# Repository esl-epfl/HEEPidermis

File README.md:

# Welcome!

HEEPidermis is a chip based on the open-source RISC-V platform [X-HEEP](https://github.com/esl-epfl/x-heep) intended to record Galvanic Skin Response (GSR) and Impedance (Z).
HEEPidermis is capable of injecting arbitrary-wave currents on the skin with an 8-bit iDAC and measure voltage through a 14-bit VCO-based ADC.
Parameters of the iDAC and ADC can be programmed dynamically using the on-board Ibex CPU. Acquired data can be stored in the 16 kB RAM memory for on-chip processing, compression, and transmission.

HEEPidermis can be interfaced through JTAG for code-debugging, SPI to obtain recordings from memory, or UART.
External ADCs and peripherals can also be commanded via SPI.

The Direct Memory Access (DMA) block allows the chip to operate autonomously without the constant interaction of the CPU. Given proper configuration, the DMA can take care of controlling the current injection profile, read data from the local ADC (or an external one), store data and/or transmit it through SPI.
The DMA can additionally re-direct data to a digital Level Crossing (dLC) block to filter data and reduce the output data rate. The output of the dLC can be stored in memory (along timestamps) or be exposed to be used as feedback loop for the analog front-end, interface with transmission circuits or as input to Spiking Neural Networks.
The dLC block also accepts inputs from analog LC ADCs (instead of the on-chip ADC).

HEEPidermis can also decimate 1-bit ΔΣ-ADCs' output with an integrated CIC filter or, alternatively, with an integrated custom smoothing stage, followed by the dLC block.

Being based on the X-HEEP platform, you can check its documentation on how to program, debug, or understand how it was built. We suggest using the [vendorized X-HEEP's documentation](../../hw/vendor/x-heep/docs/source/index.rst).
For all HEEPidermis-specific documentation, please refer to the documentation below.

<p align="center">

&nbsp;&nbsp;&nbsp;

</p>

## Index

- **Analog Front End**
  - [Analog subsystem](hw/ip/analog_subsystem/README.md)
  - [iDAC](hw/vendor/analog-library/iDAC/docs/README.md)
  - [VCO](hw/vendor/analog-library/VCO/docs/README.md)

- **Digital Back End**
  - [CPU](./docs/source/DBE/CPU.md)
  - [DMA (how we use it)](./docs/source/DBE/DMA.md)
  - [DMA](hw/vendor/x-heep/docs/source/Peripherals/DMA.md)
  - [SPI host](hw/vendor/x-heep/docs/source/Peripherals/SPI.md)
  - [SPI slave](hw/vendor/x-heep/docs/source/Peripherals/SPI_slave.md)
  - [digital Level-Crossing](hw/vendor/x-heep/docs/source/ExternalPeripherals/dLC.md)
  - [ΔΣ decimation (CIC filter)](./docs/source/DBE/CIC_filter.md)
  - [ΔΣ decimation (SES filter)](./docs/source/DBE/SES_filter.md)

- **PCBs**
  - [CHEEP-boards](./hw/vendor/cheep-boards/) - To program and provide power
  - [Breakout board](./hw/vendor/breakout-board/) - To solder the cheep and connect it to the CHEEP-boards.

- **Software**
  - [Desktop GUI](./sw/gui/README.md) - multi-device acquisition workspace (HEEPidermis board control, VCO GSR recordings, BIOPAC)

- **Reference**
  - [Register index](./docs/source/Register_index.md) - full register map of the external peripherals (iDAC, VCO decoder, REFs, aMUX, dLC, CIC, SES) with names, C-definable aliases, addresses, bit fields, reset values and descriptions. Intended to configure the cheep from an external master (e.g. an Arduino) through the SPI slave.

- **Related documents**
  - [HEEPidermis](https://arxiv.org/abs/2509.04528)
  - [ΔΣ Decimation theory](https://ieeexplore.ieee.org/abstract/document/11044062)
  - [iDAC precursor](https://ieeexplore.ieee.org/document/11044212)
  - [VCO Design](https://arxiv.org/abs/2509.06698)

## Desktop GUI

HEEPidermis includes a desktop GUI to configure the board, build firmware, record GSR signals, and visualize and analyze recordings. Adjust the injected current and sampling frequency live, explore saved recordings, and export your data to CSV.

Launch it from the repository root with:

```sh
make gui
```

See the [GUI documentation](./sw/gui/README.md) for installation requirements and usage instructions.

## BIOPAC live GUI

An experimental native Linux acquisition layer records and plots EDA from a
BIOPAC MP160 (with EDA100C or BioNomadix PPGED-R) over UDP, with live
voltage/conductance/tonic-phasic plots, manual amplifier gain and filter
declarations, and verified, autosaved sessions. No Windows, Wine, or BHAPI DLL
is required. It runs inside the desktop workspace (`make gui`, enable BIOPAC in
the device list) or standalone:

```sh
make biopac            # current BioNomadix setup: channel 9, 100 Hz, 5 µS/V
BIOPAC_ARGS=--demo make biopac   # explicitly labelled simulation
```

See the [BIOPAC documentation](./sw/gui/sdk/biopac/README.md) for setup, calibration, and safety notes.

## Evaluating trade-offs in GSR recording

HEEPidermis is a complex SoC, and acquiring GSR keepeing a proper range, sensitivity, dynamic range, resolution and power can be very tricky! To aid in the process of choosing the right parameters we have modeled the performance and consumption of our front-end and integrated it into a visual model with which you can play.

You can use the plotter in two different ways:

1. **Forward control**: You choose the operating variables (injected current and sampling frequency) and study the obtained sensitivity for a given baseline value of conductivity (G)
2. **Target**: You select a target sensitivty and power consumption and let the tool find the optimal configuration.

To view the interactive plotter on your browser (forward mode only) run:
```
make plotter
```

## Making a GSR recording

We make GSR recordings by biasing the skin to the LDO's output at 0.8 V and using a second electrode to train current from the skin using the iDAC. The VCO measures that same node and the CPU computes the drop (knowing the LDO's output).

Because the computation is far from trivial we have added [a GSR SDK](./sw/external/lib/sdk/GSR) that takes care of managing peripherals and parameters to do the correct conversion to skin's conductance in nS. You can run the example application:

```
make app PROJECT=test_reconstruction BOOT_MODE=force
make verilator-run BOOT_MODE=force # Takes long, be patient :P (or cancel anytime with Ctrl+C and go ahead with the next step)
make verilator-waves
```

You will be able to see the input resistance (in Ω) and at the top (in yellow) the computed conductance (in nS). This simulation uses the behavioral models of the front-end, including an approximation of the VCO's measured phase noise.

## Prerequisites

Since this project is based on _X-HEEP_, it has the same prerequisites.

1. Follow _X-HEEP_'s [_Prerequisite_](https://github.com/esl-epfl/x-heep/tree/main#prerequisite) section to download the necessary tools.
To correctly generate hardware and software, an extended version of the _core-v-mini-mcu_ environment is required. To install it run:
   ```Bash
   make conda
   ```
Make sure the Conda environment is active:
   ```Bash
   conda activate heepidermis
   ```

2. Make sure that the following tools are available in your system's `PATH`:
   - To compile code: **RISC-V toolchain version 2022.01.17**, supporting at least `rv32imc`. Newer versions will work but compilation will have a bug when reporting memory usage.
   - To format SystemVerilog (in case you want to open a PR): **Verible version 0.0-4023-gc1271a00**
   - To simulate (open source): **Verilator 4.210**
   - To see waveforms out of Verilator: **GTKWave**
   - In case you have the licences:
     - Siemens QuestaSim version 2020.4 or above
     - Synopsys Design Compiler version 2020.09 or above

You can follow the instructions on how to install these tools on the [X-HEEP documentation - Manual setup](https://x-heep.readthedocs.io/en/latest/GettingStarted/Setup.html#manual-setup).

## Preparing the Boards

The easiest way to test HEEPidermis is to use the [CHEEP-boards](./hw/vendor/cheep-boards/), which provide all the tools (sw and hardware) to supply power and program HEEPidermis.

HEEPidermis is soldered (or placed on a socket) on the [breakout board](./hw/vendor/breakout-board/).

After soldering everything, you also need to:

### Connect chewing-gums

The chewing-gum (CG) boards are small shields that are connected to the main board, and which can be used to provide power or reference voltages to HEEPidermis, and measure that consumption.

| CG | Function | Nominal value | CG | Function | Nominal value |
| :--- | :--- | :--- | :--- | :--- | :--- |
| 6 | DCORE VDD | 0.8 V | 7 | ACORE VDD | 1.2 V |
| 5 | IO VDD | 1.8 V | 8 | iREF | Connect a source of 400 nA |
| 4 | not used | - | 9 | REF VDD | 1.2 V |
| 3 | not used | - | 10 | LDO VREF | 0.8 V |
| 2 | not used | - | 11 | VCO VDD | 0.8 V |
| 1 | not used | - | 12 | LDO VDD | 1.2 V |

> _Note that the bottom three CGs on the picture below are not used, they are just used to inject voltages here and there with an external cable for testing._

⚠️ Remember to solder a shunt resistor below the CG! ~10 Ω should do fine for the range 1-100 µW. Consider that the INA will amplify the drop by 1000-2000×, has an offset of some 10s µV, and it cannot output more than 3.3 V.

### Connect jumpers and switches

On the main board
* Each CG has three jumpers. To control them with the trimmer, connect the jumper next to it towards its screw. Connect the jumper on the side away from the trimmer to turn the power on. Connect the jumper innermost to the main baord away from the test point to make the output go to the main board.
* Connect the jumper for the IO VDD (next to CG 8) on 1.8 V
* No need to connect any jumper next to the oscilaltor (bottom of the main board)

On the breakout board there are several places where to connect jumpers to use the cheep on different configurations. Mainly, there are two rulers of pin headers around the cheep which can be used to connect or disconnect supplies. Many of them are short-circuited on both sides, so you just use the headers as test points or to inject a signal. The rest are marked with what would get to the cheep if you close the jumper. Additionally there are three-pin jumpers for you to choose what to supply the cheep with: an ideal supply coming from the main board's chewing gums, or a voltage/current coming from the on-cheep supplies.

Check the table on [the breakout board's readme](./hw/vendor/cheep-boards/) to see what connects what.

> ❗There are two pads on the bottom of the board that need to be short-circuited: They will connect the clock input to the cheep. You can select where to take the clock, if you have no clue what to do, put some solder tin on the two pair of pads that point to the main board to take the clock from there. Don't worry if you make a mistake and short a bit the other, it's not the end of the world.

There is a pair of switches on the breakout board, to the left of the cheep. You can eiter solder the switches to select the boot mode, or you can short with tin them the mid-pin with the one closest to the cheep to only use JTAG mode (explained below).

### Bug correction

🪲 You need to cut the pin below the `value` pin (the outter most pin, in row 31 of the main board) in the connector to the main board or nothing will work, sorry.

## Programming the ASIC

You can program the ASIC through 3 alternatives:
 - JTAG
 - Loading an external flash that HEEPidermis can read through SPI
 - Loading the program in RAM through the SPI slave peripheral

### Programming through JTAG

You need to connect the JTAG interface to an FTDI chip. This is avaialble on the [EPFL programmer](https://github.com/esl-epfl/x-heep-programmer-pmod) or on the [CHEEP boards](https://eslgit.epfl.ch/heep/cheep-boards) (currently only available upon request).

1. The BOOT switches should be set to

| Signal     | Value |
|------------|-------|
| FLASH_EXEC | 0     |
| BOOT_SEL   | 0     |

2. Set the system clock to 1 MHz. You can do that in two steps if you have the CHEEP board, and have exported the variable `$CHEEP_BOARDS` pointing to the folder where the repo is.
```bash
make board_config
make board_freq PLL_FREQ=1_000_000  #default
```

3. Build the SW/HW stack of the cheep
```bash
make cheep-gen
```

4. Compile the code
```bash
make app BOOT_MODE=jtag
```

1. Open openOCD and picocom to see the UART output
```bash
make jtag_open
```
1. Open GDB and run the program
```bash
make jtag_run
```
Useful commands:
> `c` (continue)
>
> `monitor reset hart`
>
> `monitor pc _start`
>
> `si` (next instruction)
>
> `disassembler`
>
> `x/8i` (see the following instructions).

1. Exit GDB with `ctrl+C` and type `quit`
2. Close the openOCD and uart terminals with
```bash
make jtag_close
```

### Programming from the FLASH

Testing... we seem to have a bug on the main board that prevents this from working 😬

### Programming through SPI

HEEPidermis supports SRAM programming through its SPI slave interface using a Raspberry Pi Pico. The Pico also provides a configurable external system clock.

The system supports operation from the ASIC's internal VCOp oscillator, allowing the external clock to be disconnected after initialization.

For hardware connections, programming commands, clock configuration, VCO-based clock operation, and troubleshooting, see the **[SPI Programmer and Clock Configuration Guide](./sw/arduino/README.md)**.

## RTL Simulation

The included [`makefile`](./makefile) proves all the necessary rules to build _HEEPidermis_:

1. Generate all the RTL files (and software headers):
   ```bash
   make cheep-gen
   ```
   Some _X-HEEP_ configuration parameters (e.g. `BUS`, `MEMORY_BANKS` etc.) are still supported, although the default configuration may differ (check [`peripherals_config`](./config/peripherals_config)). In general, these should not be passed through the makefile targets but should be configured in the hjson files in the `config` folder.

2. Build the simulation model:
   ```bash
   make verilator-build     # Verilator
   make questasim-build     # QuestaSim
   ```

3. The software build process is primarily handled by _X-HEEP_, and most of its [example applications](./hw/vendor/x-heep/sw/applications/) will work on _HEEPidermis_ as well. You can choose other `BOOT_MODE`, just be sure to match it with the one used with `make *-build` (by default they use `fore`). `force` will be the faster for simulation.

```bash
make app PROJECT=test_dlc_vco BOOT_MODE=force
```

The combinations of compatible linker and boot modes can be found here:

1. Launch the simulation with the compiled firmware:
   ```bash
   make verilator-run       # Verilator with waveforms dump
   make verilator-opt       # Verilator without waveforms dump
   make questasim-run       # QuestaSim
   make questasim-gui       # QuestaSim with GUI
   ```

   You can also set other parameters like the `FUSESOC_FLAGS`, `LOG_LEVEL`, `BOOT_MODE`, `VCD_MODE`, etc. to customize the simulation. Refer to the [`makefile`](./makefile) for more details.

2. _HEEPidermis_ `stdout` is exposed through a UART DPI interface at `/dev/pts/<N>`, where `N` is a number printed on the simulation log during execution. You can connect to it using `screen` or similar tools, e.g.:
   ```bash
   screen /dev/pts/0
   ```
   The UART output is also stored to the `uart.log` file in the common simulation directory (`build/sim-common/uart.log`).
   > Using `printf()` will significantly increase the firmware execution time and therefore the simulation. For quick debugging, it recommended to use the return value from `main` instead. When it is _not_ zero, the testbench will print it out at the end of the simulation.

3. The waveforms dumped during the simulation can be opened using:
   ```bash
   make verilator-waves # after Verilator simulation
   make questasim-waves # after QuestaSim simulation
   ```

This will open the waveforms (example from `test_dlc_vco` application):

Assuming that your firmware is already available, steps 1., 3., and 4. can be repeated with a single command using the `verilator-sim` or `questasim-sim` targets.

# Questions?

Have questions? curiosities? ideas on how to exploit HEEPidermis? Want to contribute on following versions of the SoC?
Drop an email :) juan.sapriza@epfl.ch

# 📄 Reference

Want to know more details? Found HEEPidermis useful for your research? Cite our [LASCAS paper](https://ieeexplore.ieee.org/document/11457136).

```
@INPROCEEDINGS{11457136,
  author={Sapriza, Juan and Grassano, Beatrice and Naclerio, Alessio and Quadri, Filippo and Terzano, Tommaso and Mallasén, David and Schiavone, Davide and Leplae, Robin and Moullet, Jérémie and Levisse, Alexandre and Müller, Christoph and Graziano, Mariagrazia and Miguez, Matías and Atienza, David},
  booktitle={2026 IEEE 17th Latin America Symposium on Circuits and System (LASCAS)},
  title={HEEPidermis: A Versatile SoC for BioZ Recording},
  year={2026},
  pages={1-5},
  doi={10.1109/LASCAS67804.2026.11457136}}
```

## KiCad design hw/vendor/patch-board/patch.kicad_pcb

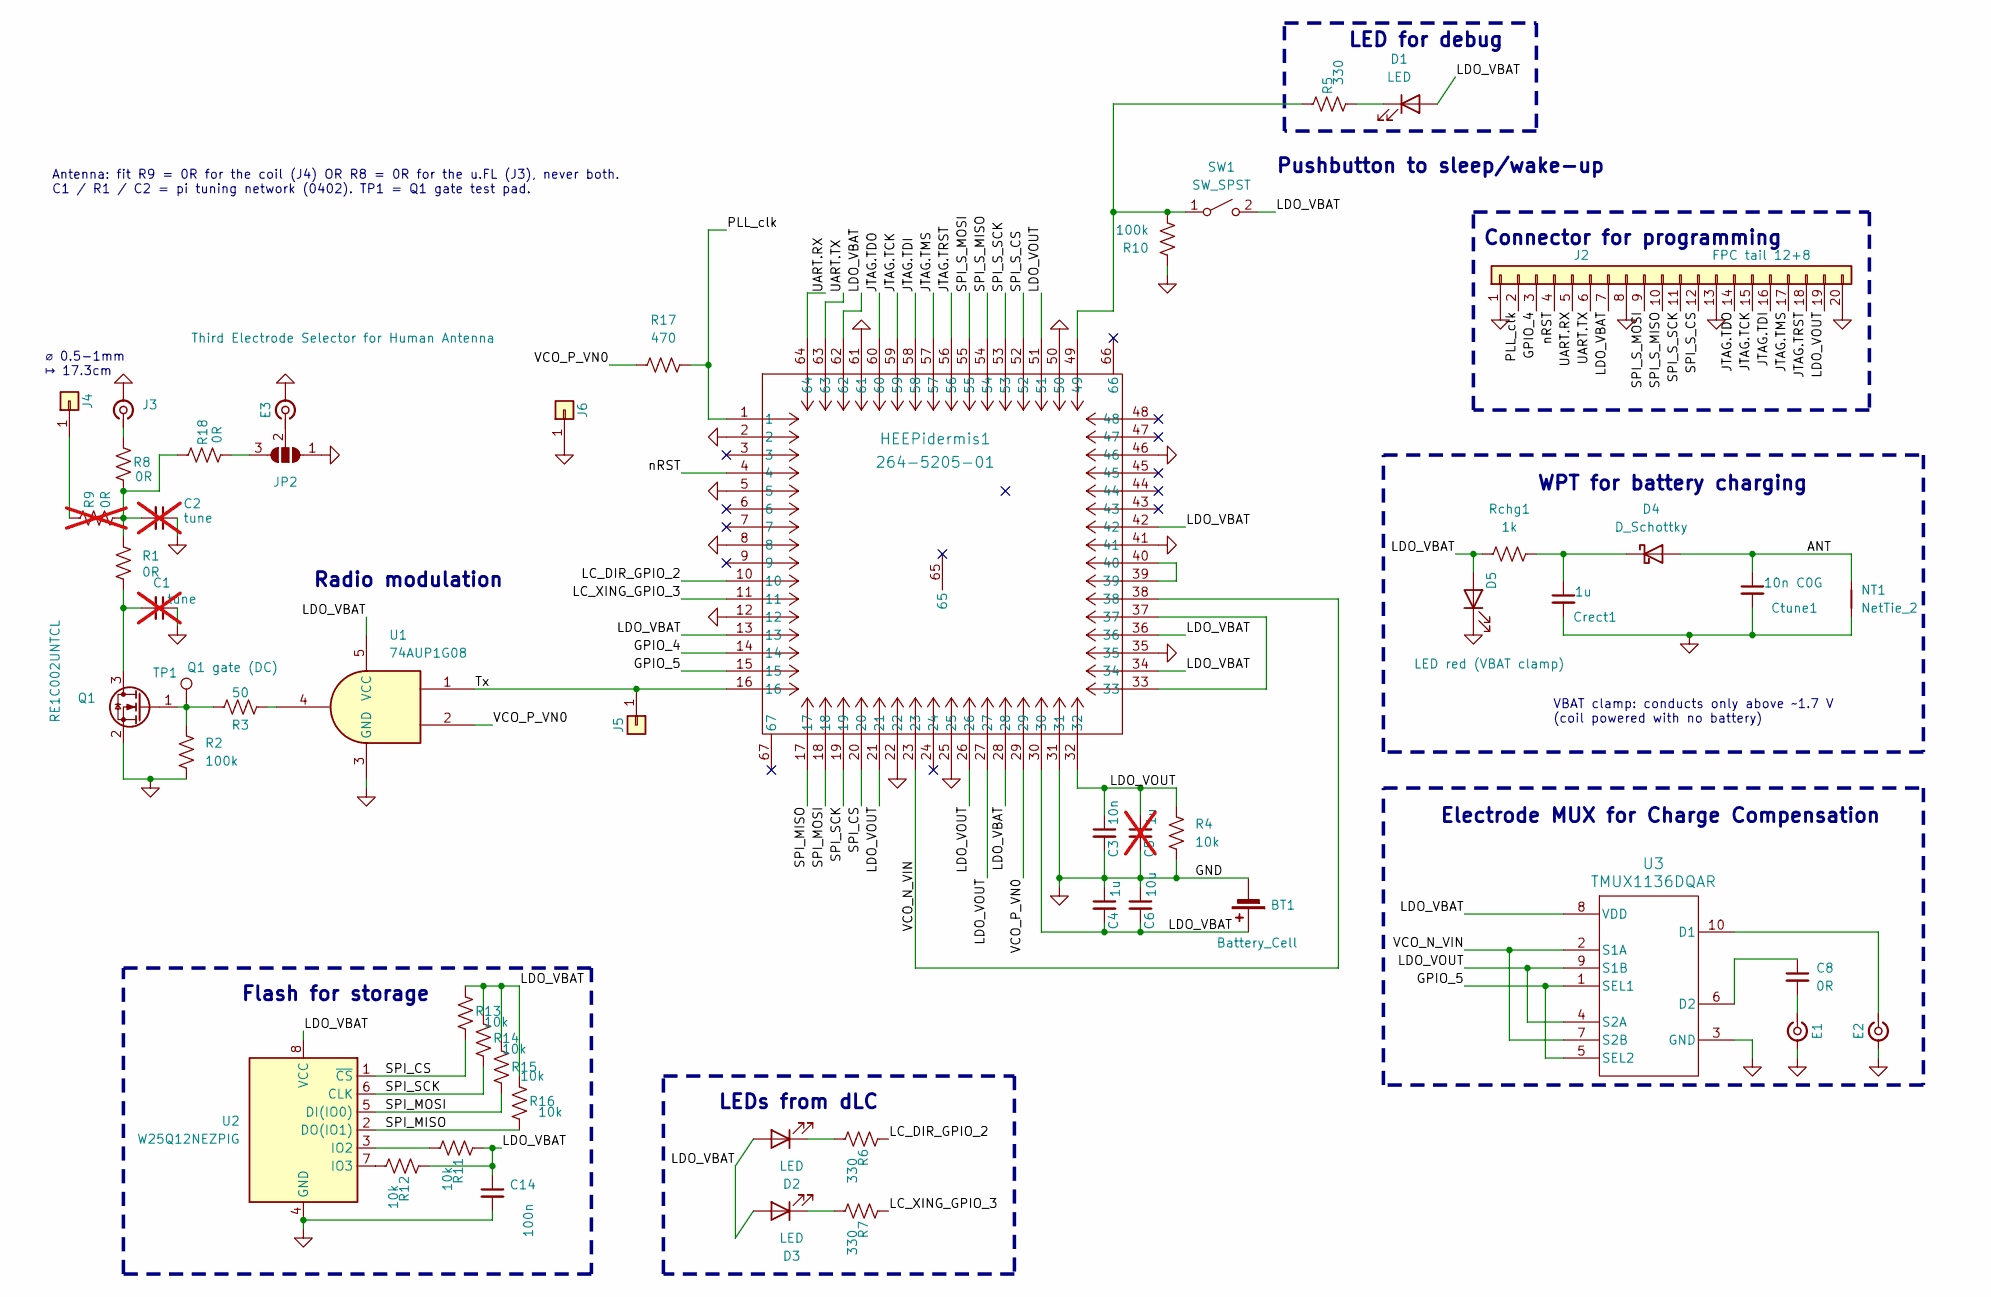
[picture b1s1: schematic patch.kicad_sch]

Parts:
BT1: Battery_Cell; BatteryHolder_Seiko_MS621F
C1, C2: tune; C_0402_1005Metric; not fitted
C3: 10n; C_0603_1608Metric; Mouser Part Number 80-C0805C104Z3V; Digikey Part Number 399-9158-1-ND
C4: 1u; C_0603_1608Metric; Mouser Part Number 80-C0805C104Z3V; Digikey Part Number 399-9158-1-ND
C5: 1u; C_0603_1608Metric; Mouser Part Number 80-C0805C104Z3V; Digikey Part Number 399-9158-1-ND; not fitted
C6: 10u; C_0603_1608Metric; Mouser Part Number 80-C0805C104Z3V; Digikey Part Number 399-9158-1-ND
C8: 0R; C_0603_1608Metric
C14: 100n; C_0603_1608Metric; Mouser Part Number 80-C0805C104Z3V; Digikey Part Number 399-9158-1-ND
Crect1: 1u; C_0603_1608Metric; Mouser Part Number 80-C0805C104Z3V; Digikey Part Number 399-9158-1-ND
Ctune1: 10n C0G; C_0603_1608Metric
D1, D2, D3: LED; LED_0603_1608Metric
D4: D_Schottky; D_0603_1608Metric
D5: LED red (VBAT clamp); LED_0603_1608Metric
E1, E2, E3: Conn_Coaxial_Small; 4mm_snap_socket
HEEPidermis1: 264-5205-01; QFN-64-1EP_9x9mm_P0.5mm_EP3.4x3.4mm
J2: FPC tail 12+8; FPC_Tail_2x_P1.00mm_12+8
J3: Conn_Coaxial_Small; U.FL_Molex_MCRF_73412-0110_Vertical
J4, J5, J6: Conn_01x01; PinHeader_1x01_P2.54mm_Vertical
JP2: Third Electrode Selector for Human Antenna; SolderJumper-3_P1.3mm_Open_RoundedPad1.0x1.5mm
NT1: NetTie_2; 1MHz_coil_29x14
Q1: RE1C002UNTCL; SOT-416
R1, R8, R18: 0R; R_0402_1005Metric
R2, R10: 100k; R_0603_1608Metric
R3: 50; R_0603_1608Metric
R4, R11, R12, R13, R14, R15, R16: 10k; R_0603_1608Metric
R5, R6, R7: 330; R_0603_1608Metric
R9: 0R; R_0402_1005Metric; not fitted
R17: 470; R_0603_1608Metric
Rchg1: 1k; R_0603_1608Metric
SW1: SW_SPST; SPST_1.6x3mm
TP1: Q1 gate (DC); TestPoint_Pad_D1.0mm
U1: 74AUP1G08; SOT-353_SC-70-5_Handsoldering
U2: W25Q12NEZPIG; SOIC-8_5.23x5.23mm_P1.27mm
U3: TMUX1136DQAR; DQA0010A

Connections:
/ANT: Ctune1.1, D4.2 (A), NT1.2
/GPIO_4: HEEPidermis1.14, J2.3
/GPIO_5: HEEPidermis1.15, U3.1 (SEL1), U3.5 (SEL2)
/JTAG.TCK: HEEPidermis1.59, J2.15
/JTAG.TDI: HEEPidermis1.58, J2.16
/JTAG.TDO: HEEPidermis1.60, J2.14
/JTAG.TMS: HEEPidermis1.57, J2.17
/JTAG.TRST: HEEPidermis1.56, J2.18
/LC_DIR_GPIO_2: HEEPidermis1.10, R6.2
/LC_XING_GPIO_3: HEEPidermis1.11, R7.2
/LDO_VBAT: BT1.1 (+), C4.2, C6.2, C14.1, D1.2 (A), D2.2 (A), D3.2 (A), D5.2 (A), HEEPidermis1.13, HEEPidermis1.28, HEEPidermis1.30, HEEPidermis1.34, HEEPidermis1.36, HEEPidermis1.42, HEEPidermis1.62, J2.7, R11.2, R12.2, R13.2, R14.2, R15.2, R16.2, Rchg1.1, SW1.2 (B), U1.5 (VCC), U2.8 (VCC), U3.8 (VDD)
/LDO_VOUT: C3.1, C5.1, HEEPidermis1.21, HEEPidermis1.26, HEEPidermis1.27, HEEPidermis1.32, HEEPidermis1.51, J2.19, R4.1, U3.4 (S2A), U3.9 (S1B)
/PLL_clk: HEEPidermis1.1, J2.2, R17.2
/SPI_CS: HEEPidermis1.20, R13.1, U2.1 (~CS)
/SPI_MISO: HEEPidermis1.17, R16.1, U2.2 (DO(IO1))
/SPI_MOSI: HEEPidermis1.18, R15.1, U2.5 (DI(IO0))
/SPI_SCK: HEEPidermis1.19, R14.1, U2.6 (CLK)
/SPI_S_CS: HEEPidermis1.52, J2.12
/SPI_S_MISO: HEEPidermis1.54, J2.10
/SPI_S_MOSI: HEEPidermis1.55, J2.9
/SPI_S_SCK: HEEPidermis1.53, J2.11
/Tx: HEEPidermis1.16, J5.1 (Pin_1_1), U1.1
/UART.RX: HEEPidermis1.64, J2.5
/UART.TX: HEEPidermis1.63, J2.6
/VCO_N_VIN: HEEPidermis1.23, HEEPidermis1.38, U3.2 (S1A), U3.7 (S2B)
/VCO_P_VN0: HEEPidermis1.29, R17.1, U1.2
/nRST: HEEPidermis1.4, J2.4
GND: BT1.2 (-), C1.1, C2.1, C3.2, C4.1, C5.2, C6.1, C14.2, Crect1.2, Ctune1.2, D5.1 (K), E1.2 (Ext), E2.2 (Ext), E3.2 (Ext), HEEPidermis1.2, HEEPidermis1.5, HEEPidermis1.8, HEEPidermis1.12, HEEPidermis1.22, HEEPidermis1.25, HEEPidermis1.31, HEEPidermis1.35, HEEPidermis1.41, HEEPidermis1.46, HEEPidermis1.50, HEEPidermis1.61, J2.1, J2.8, J2.13, J2.20, J3.2 (Ext), J6.1 (Pin_1_1), JP2.1 (A), NT1.1, Q1.2 (S), R2.1, R4.2, R10.2, U1.3 (GND), U2.4 (GND), U3.3 (GND)
unnamed: C2.2, R1.2, R8.1, R9.1, R18.2
unnamed: D1.1 (K), R5.1
unnamed: D2.1 (K), R6.1
unnamed: D3.1 (K), R7.1
unnamed: Crect1.1, D4.1 (K), Rchg1.2
unnamed: C8.2, E1.1 (In_1)
unnamed: E2.1 (In_1), U3.10 (D1)
unnamed: E3.1 (In_1), JP2.2 (C)
unnamed: HEEPidermis1.33, HEEPidermis1.37
unnamed: HEEPidermis1.39, HEEPidermis1.40
unnamed: J3.1 (In), R8.2
unnamed: J4.1 (Pin_1_1), R9.2
unnamed: JP2.3 (B), R18.1
unnamed: C1.2, Q1.3 (D), R1.1
unnamed: Q1.1 (G), R2.2, R3.1, TP1.1 (1_1)
unnamed: R3.2, U1.4
unnamed: HEEPidermis1.49, R5.2, R10.1, SW1.1 (A)
unnamed: R11.1, U2.3 (IO2)
unnamed: R12.1, U2.7 (IO3)
unnamed: C8.1, U3.6 (D2)

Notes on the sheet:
LED for debug
Antenna: fit R9 = 0R for the coil (J4) OR R8 = 0R for the u.FL (J3), never both. C1 / R1 / C2 = pi tuning network (0402). TP1 = Q1 gate test pad.
VBAT clamp: conducts only above ~1.7 V (coil powered with no battery)
LEDs from dLC
WPT for battery charging
⌀ 0.5-1mm ↦ 17.3cm
Electrode MUX for Charge Compensation
Flash for storage
Connector for programming
Pushbutton to sleep/wake-up
Radio modulation

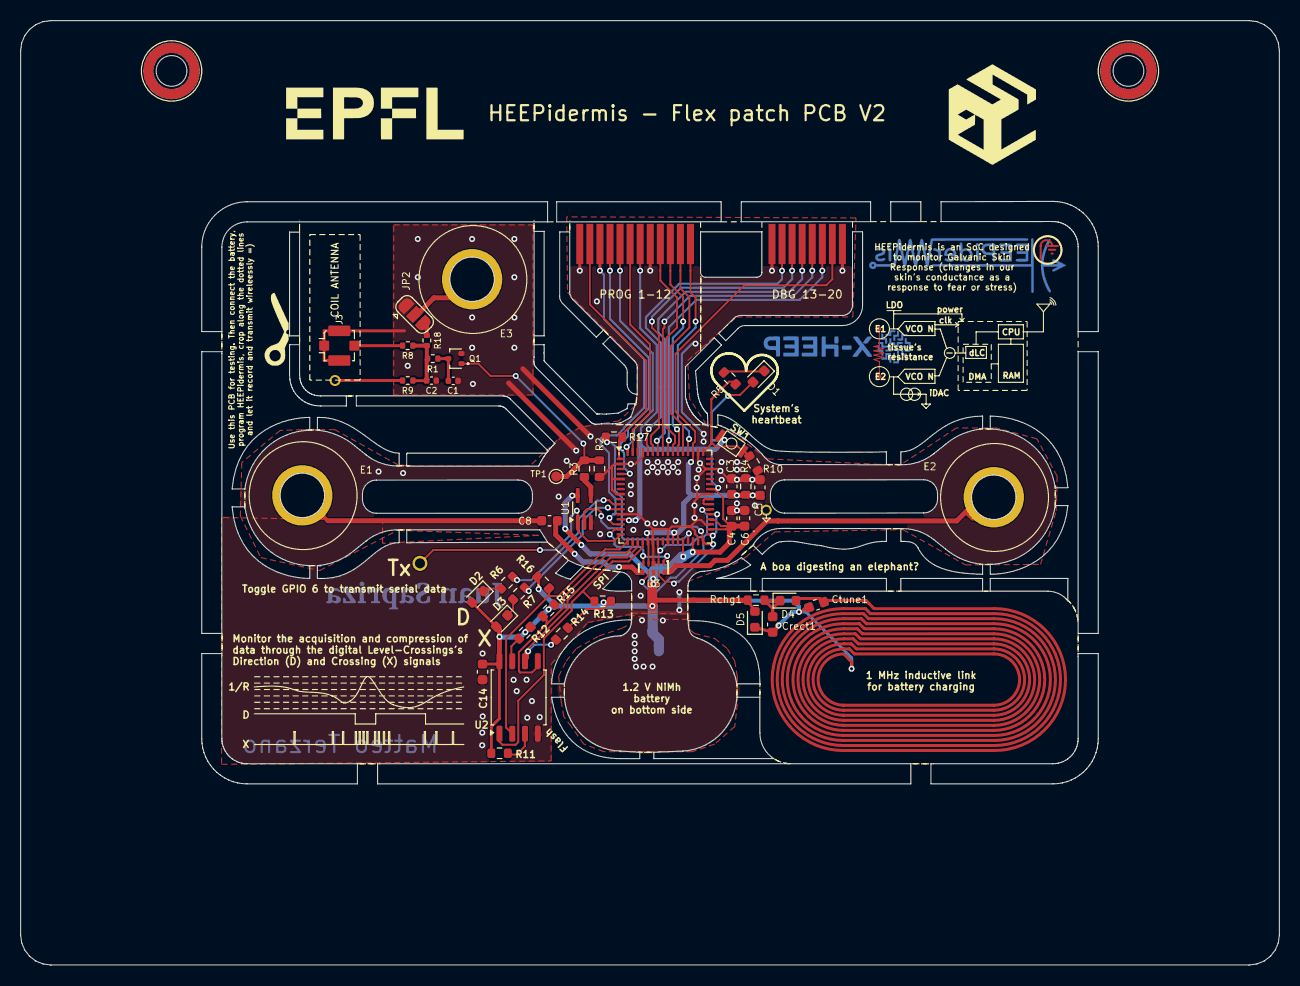
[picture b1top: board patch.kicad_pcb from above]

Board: 2 copper layers, 125.1 x 93.8 mm, 54 parts (1 on the bottom side), 48 nets.

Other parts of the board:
H1, H2: eC 3mm tooling hole; eC_tooling_hole_3mm

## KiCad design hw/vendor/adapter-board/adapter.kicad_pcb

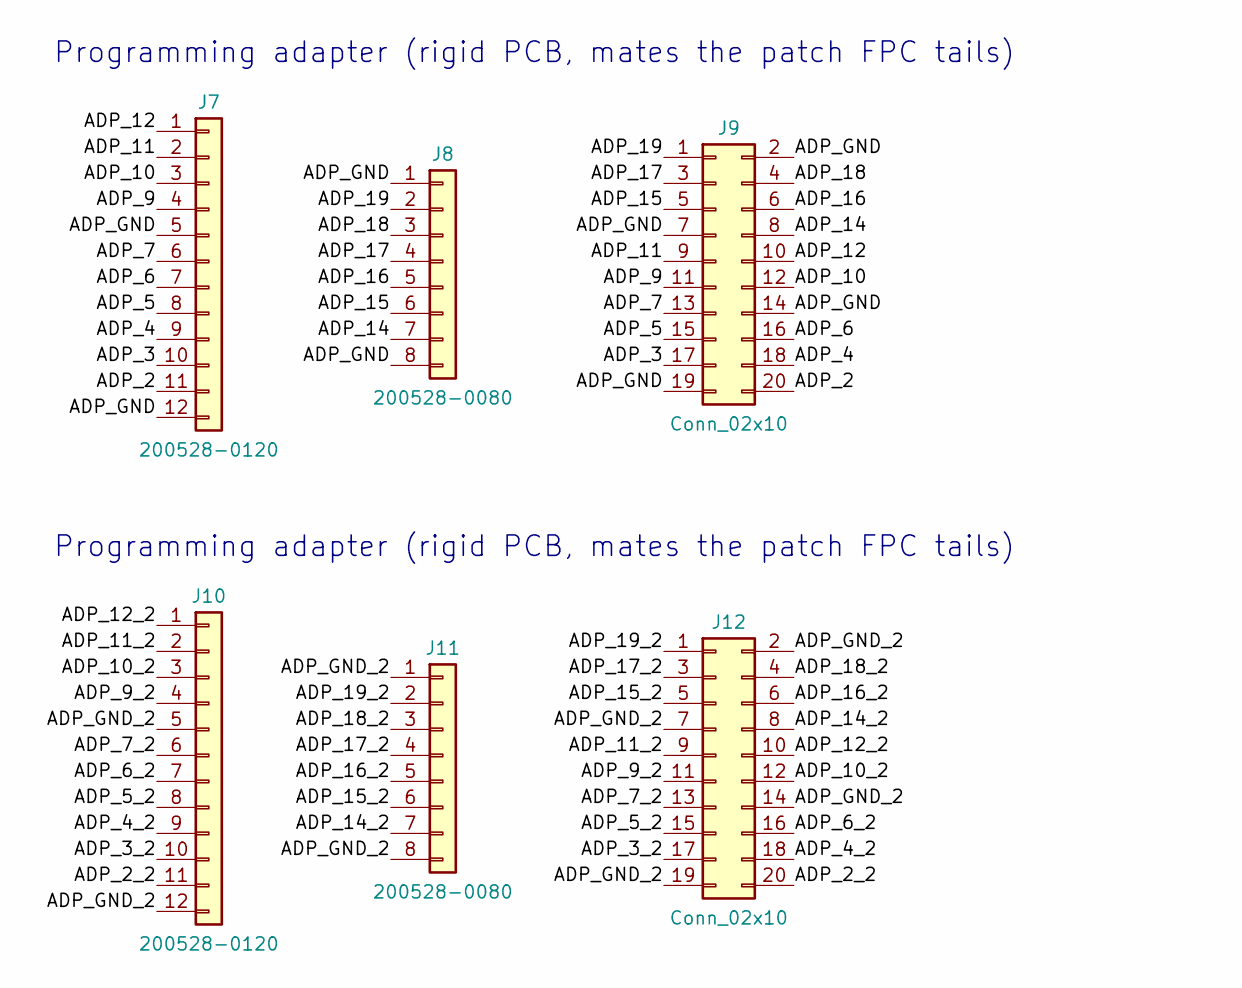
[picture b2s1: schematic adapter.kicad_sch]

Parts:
J7, J10: 200528-0120; Molex_200528-0120_1x12-1MP_P1.00mm_Horizontal
J8, J11: 200528-0080; Molex_200528-0080_1x08-1MP_P1.00mm_Horizontal
J9, J12: Conn_02x10; PinHeader_2x10_P2.54mm_Horizontal

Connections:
/ADP_2: J7.11, J9.20
/ADP_2_2: J10.11, J12.20
/ADP_3: J7.10, J9.17
/ADP_3_2: J10.10, J12.17
/ADP_4: J7.9, J9.18
/ADP_4_2: J10.9, J12.18
/ADP_5: J7.8, J9.15
/ADP_5_2: J10.8, J12.15
/ADP_6: J7.7, J9.16
/ADP_6_2: J10.7, J12.16
/ADP_7: J7.6, J9.13
/ADP_7_2: J10.6, J12.13
/ADP_9: J7.4, J9.11
/ADP_9_2: J10.4, J12.11
/ADP_10: J7.3, J9.12
/ADP_10_2: J10.3, J12.12
/ADP_11: J7.2, J9.9
/ADP_11_2: J10.2, J12.9
/ADP_12: J7.1, J9.10
/ADP_12_2: J10.1, J12.10
/ADP_14: J8.7, J9.8
/ADP_14_2: J11.7, J12.8
/ADP_15: J8.6, J9.5
/ADP_15_2: J11.6, J12.5
/ADP_16: J8.5, J9.6
/ADP_16_2: J11.5, J12.6
/ADP_17: J8.4, J9.3
/ADP_17_2: J11.4, J12.3
/ADP_18: J8.3, J9.4
/ADP_18_2: J11.3, J12.4
/ADP_19: J8.2, J9.1
/ADP_19_2: J11.2, J12.1
/ADP_GND: J7.5, J7.12, J8.1, J8.8, J9.2, J9.7, J9.14, J9.19
/ADP_GND_2: J10.5, J10.12, J11.1, J11.8, J12.2, J12.7, J12.14, J12.19

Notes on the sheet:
Programming adapter (rigid PCB, mates the patch FPC tails)

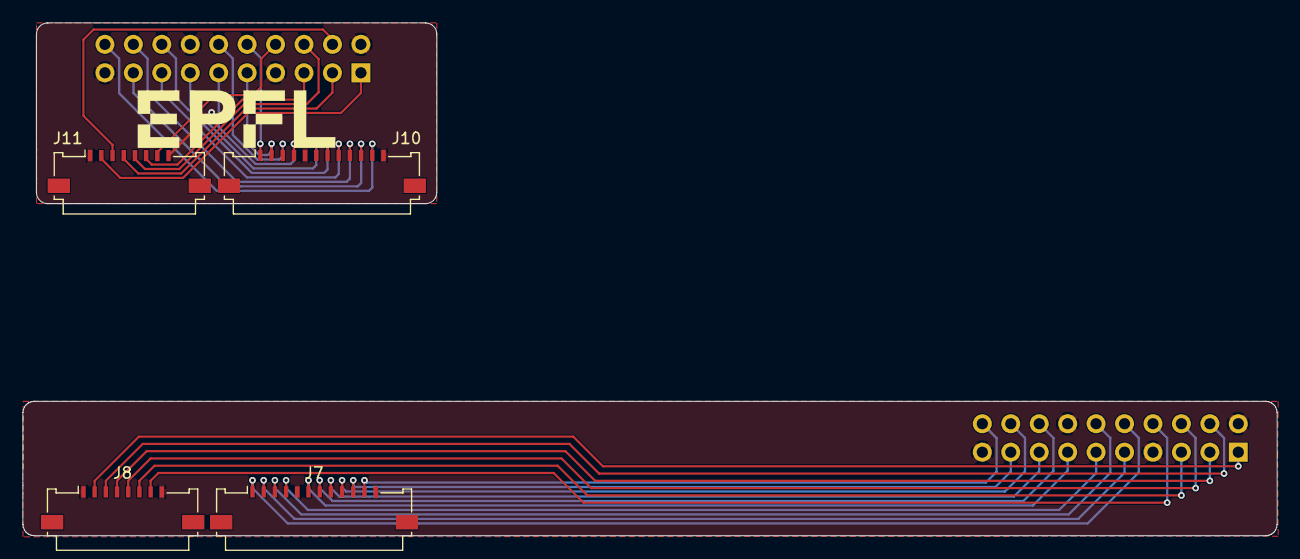
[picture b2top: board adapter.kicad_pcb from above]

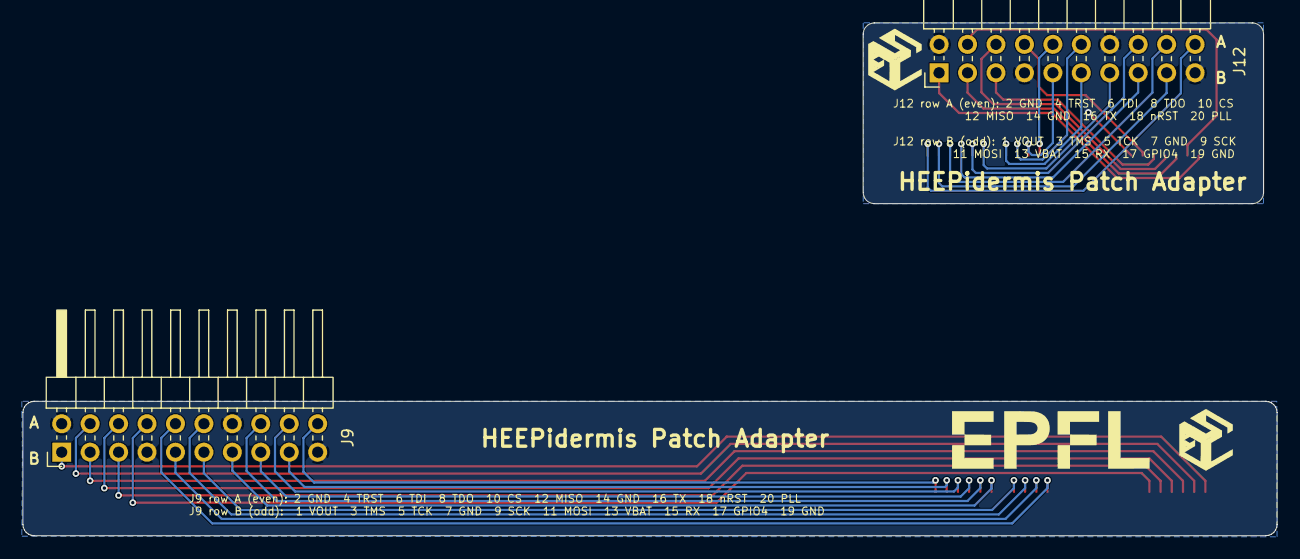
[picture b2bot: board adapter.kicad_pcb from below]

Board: 2 copper layers, 112.0 x 45.8 mm, 6 parts (2 on the bottom side), 34 nets.

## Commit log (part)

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2025-09-09 initial clean commit
2026-01-12 First attempt to use scanf. I think there is a short on HW of the main pcb
2026-04-03 Experiments with DSM
2026-04-04 Obtained plots for paper
2026-04-06 Added more plots for the SES paper
2026-04-06 Added test with dLC
2026-04-08 Tests on the dLC
2026-04-08 Updated makefile to force to update the environment and added required packages
2026-04-08 added scipy as requirement
2026-04-08 Added some hype into the readme
2026-04-13 Testing different transfers for the SES
2026-04-13 Adjusted dLC params to discard 1 bit and not take large changes as negative
2026-04-13 Added better extraction from dLC + better reconstruction
2026-04-15 Added patch to expose the last word of the tc_ram bank
2026-04-15 Added test app
2026-04-15 Accelerated UART to almost maximum
2026-04-20 Tuned plots
2026-04-22 updated plots
2026-04-22 Ported the VCO's behavioral into a polynomial and added some random noise +- 100 Hz
2026-04-22 ⚠️ MADE ALL test_GSR 100x FASTER WRT REAL TIME (resistor, vco gain and sampling frequency)
2026-04-23 Corrected transfer
2026-04-28 Comparison
2026-05-01 Added power measurement plots
2026-05-05 Added mention on the README
2026-05-05 Added Blanca's authorship
2026-05-12 Measured more CIC/SES power consumptions
2026-05-26 Added fusesoc and edalize to requirements
2026-05-26 Fixed event based application, and added reconstruction path
2026-05-27 ⚖ Automatic range adjustment (#10)
2026-06-04 characterized impact of N on digital power consumption (this commit + N-2 commit)
2026-06-04 resolution computation done and works with DMA
2026-06-04 added digital power consumption to plotter
2026-06-04 clean DMA main application
2026-06-04 playing around with dlc
2026-06-04 added read_batch for dma
2026-06-04 updated plotter to include all tradeoff plots (new analysis tabs)
2026-06-04 dma implemented in GSR_controller ! :)
2026-06-04 removed averaging idea
2026-06-04 refactored main application
2026-06-04 DMA works but no dlc (don't have the latest version). - Started reading in windows
2026-06-04 minor changes on plotter
2026-06-04 skip the first sample after init or config change
2026-06-04 moved files to evalute forlder and updated gitignore + minimal update to .gtkw
2026-06-04 finalize PR for range adjustement (no duty cycling yet)
2026-06-04 minor updated to plotter
2026-06-04 updated read_sample to read
2026-06-05 DMA handles duty cycling (PR done)
2026-06-05 adds the new FEA and comparison workflow.
